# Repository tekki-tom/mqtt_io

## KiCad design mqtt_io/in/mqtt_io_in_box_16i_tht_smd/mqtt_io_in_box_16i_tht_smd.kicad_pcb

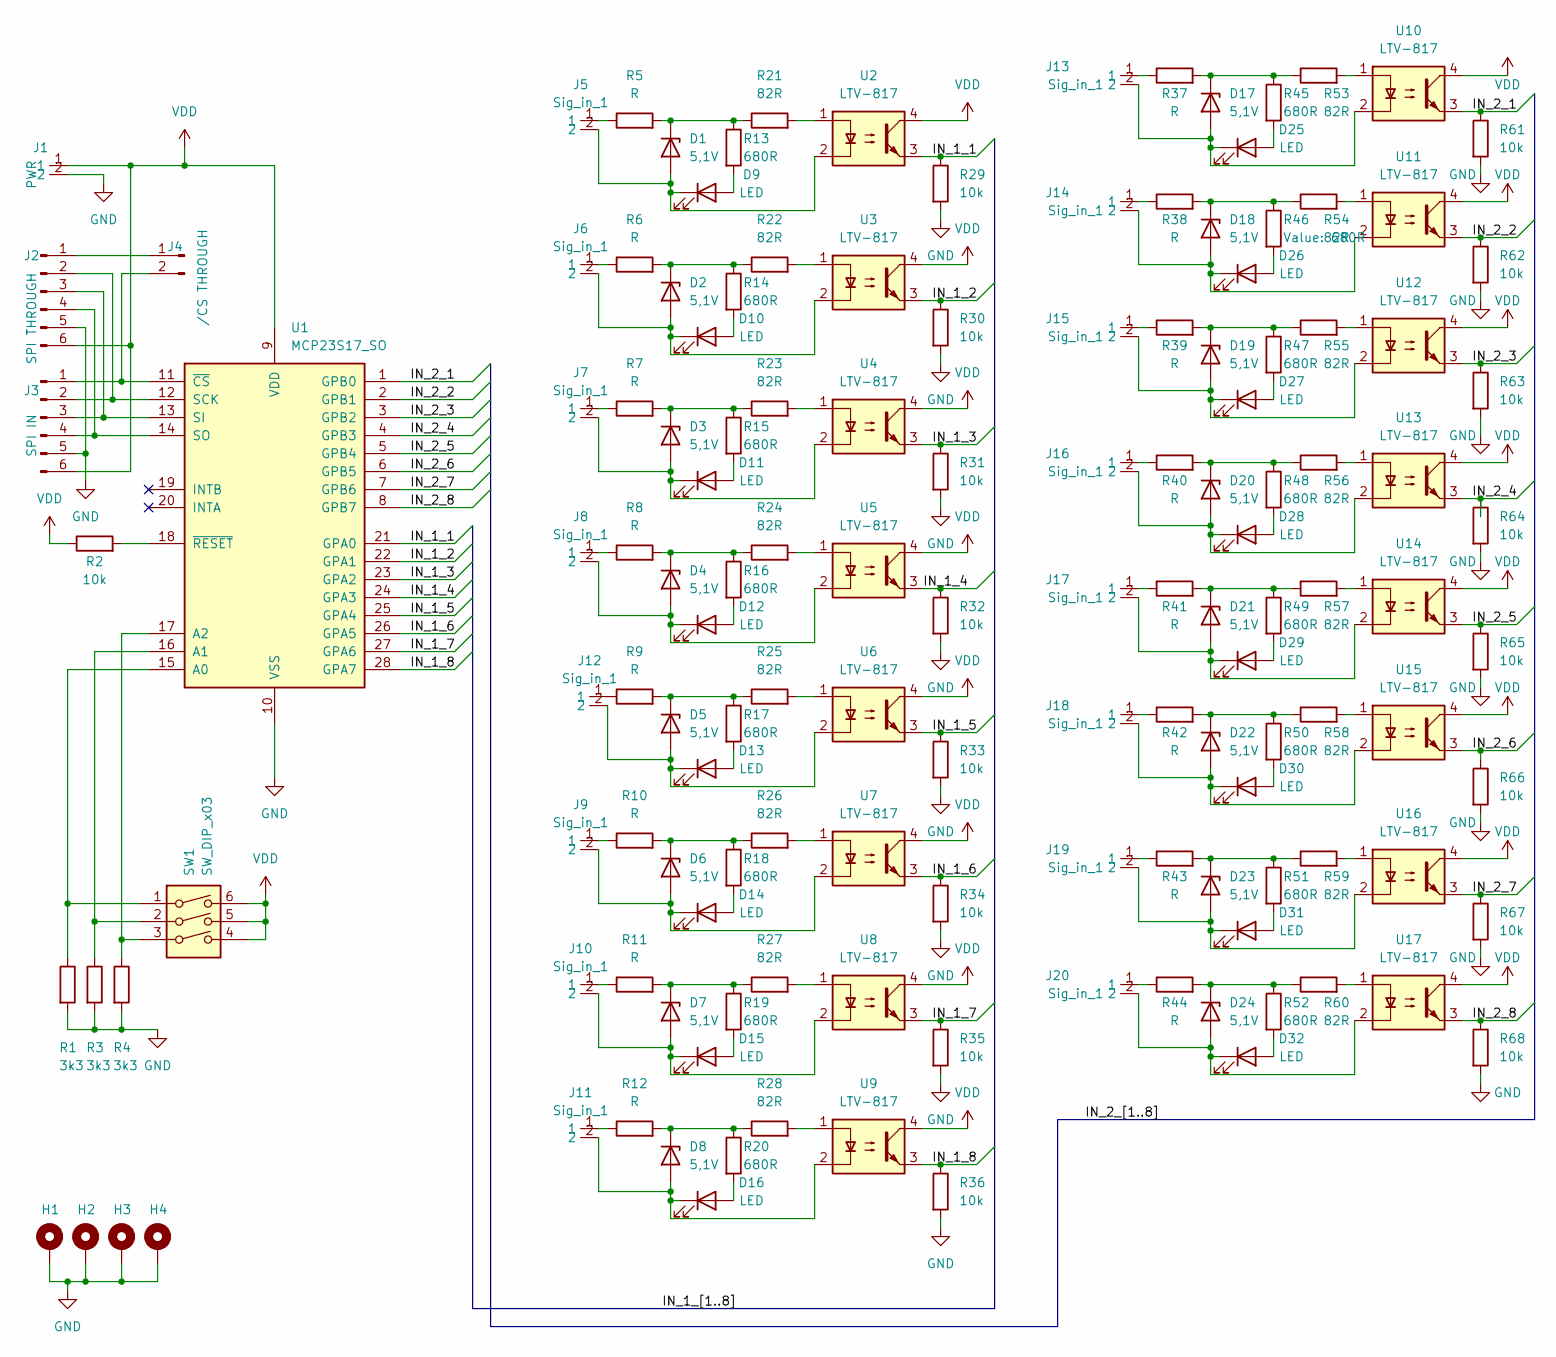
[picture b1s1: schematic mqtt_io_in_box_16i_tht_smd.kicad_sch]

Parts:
D1, D2, D3, D4, D5, D6, D7, D8, D17, D18, D19, D20, D21, D22, D23, D24: 5,1V; D_MiniMELF_Handsoldering
D9, D10, D11, D12, D13, D14, D15, D16, D25, D26, D27, D28, D29, D30, D31, D32: LED; LED_0805_2012Metric_Pad1.15x1.40mm_HandSolder
H1, H2, H3, H4: MountingHole_Pad; MountingHole_3.2mm_M3_DIN965_Pad_TopBottom
J1: PWR; AST_041-2
J2: SPI THROUGH; PinHeader_1x06_P2.54mm_Vertical
J3: SPI IN; PinHeader_1x06_P2.54mm_Vertical
J4: /CS THROUGH; PinHeader_1x02_P2.54mm_Vertical
J5, J6, J7, J8, J9, J10, J11, J12, J13, J14, J15, J16, J17, J18, J19, J20: Sig_in_1; AST_041-2
R1, R3, R4: 3k3; R_0805_2012Metric_Pad1.20x1.40mm_HandSolder
R2, R29, R30, R31, R32, R33, R34, R35, R36, R61, R62, R63, R64, R65, R66, R67, R68: 10k; R_0805_2012Metric_Pad1.20x1.40mm_HandSolder
R5, R6, R7, R8, R9, R10, R11, R12, R37, R38, R39, R40, R41, R42, R43, R44: R; R_0805_2012Metric_Pad1.20x1.40mm_HandSolder
R13, R14, R15, R16, R17, R18, R19, R20, R45, R46, R47, R48, R49, R50, R51, R52: 680R; R_0805_2012Metric_Pad1.20x1.40mm_HandSolder
R21, R22, R23, R24, R25, R26, R27, R28, R53, R54, R55, R56, R57, R58, R59, R60: 82R; R_0805_2012Metric_Pad1.20x1.40mm_HandSolder
SW1: SW_DIP_x03; DIP-6_W7.62mm_LongPads
U1: MCP23S17_SO; SOIC-28W_7.5x17.9mm_P1.27mm
U2, U3, U4, U5, U6, U7, U8, U9, U10, U11, U12, U13, U14, U15, U16, U17: LTV-817; DIP-4_W7.62mm

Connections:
/IN_1_1: R29.1, U1.21 (GPA0), U2.3
/IN_1_2: R30.1, U1.22 (GPA1), U3.3
/IN_1_3: R31.1, U1.23 (GPA2), U4.3
/IN_1_4: R32.1, U1.24 (GPA3), U5.3
/IN_1_5: R33.1, U1.25 (GPA4), U6.3
/IN_1_6: R34.1, U1.26 (GPA5), U7.3
/IN_1_7: R35.1, U1.27 (GPA6), U8.3
/IN_1_8: R36.1, U1.28 (GPA7), U9.3
/IN_2_1: R61.1, U1.1 (GPB0), U10.3
/IN_2_2: R62.1, U1.2 (GPB1), U11.3
/IN_2_3: R63.1, U1.3 (GPB2), U12.3
/IN_2_4: R64.1, U1.4 (GPB3), U13.3
/IN_2_5: R65.1, U1.5 (GPB4), U14.3
/IN_2_6: R66.1, U1.6 (GPB5), U15.3
/IN_2_7: R67.1, U1.7 (GPB6), U16.3
/IN_2_8: R68.1, U1.8 (GPB7), U17.3
GND: H1.1, H2.1, H3.1, H4.1, J1.2, J2.5, J3.5, R1.2, R3.2, R4.2, R29.2, R30.2, R31.2, R32.2, R33.2, R34.2, R35.2, R36.2, R61.2, R62.2, R63.2, R64.2, R65.2, R66.2, R67.2, R68.2, U1.10 (VSS)
unnamed: D1.2 (A), D9.1 (K), J5.2, U2.2
unnamed: D1.1 (K), R5.2, R13.1, R21.1
unnamed: D2.1 (K), R6.2, R14.1, R22.1
unnamed: D3.1 (K), R7.2, R15.1, R23.1
unnamed: D4.1 (K), R8.2, R16.1, R24.1
unnamed: D5.1 (K), R9.2, R17.1, R25.1
unnamed: D6.1 (K), R10.2, R18.1, R26.1
unnamed: D7.1 (K), R11.2, R19.1, R27.1
unnamed: D8.1 (K), R12.2, R20.1, R28.1
unnamed: D9.2 (A), R13.2
unnamed: D10.2 (A), R14.2
unnamed: D2.2 (A), D10.1 (K), J6.2, U3.2
unnamed: D11.2 (A), R15.2
unnamed: D3.2 (A), D11.1 (K), J7.2, U4.2
unnamed: D12.2 (A), R16.2
unnamed: D4.2 (A), D12.1 (K), J8.2, U5.2
unnamed: D13.2 (A), R17.2
unnamed: D5.2 (A), D13.1 (K), J12.2, U6.2
unnamed: D14.2 (A), R18.2
unnamed: D6.2 (A), D14.1 (K), J9.2, U7.2
unnamed: D15.2 (A), R19.2
unnamed: D7.2 (A), D15.1 (K), J10.2, U8.2
unnamed: D16.2 (A), R20.2
unnamed: D8.2 (A), D16.1 (K), J11.2, U9.2
unnamed: D17.2 (A), D25.1 (K), J13.2, U10.2
unnamed: D17.1 (K), R37.2, R45.1, R53.1
unnamed: D18.2 (A), D26.1 (K), J14.2, U11.2
unnamed: D18.1 (K), R38.2, R46.1, R54.1
unnamed: D19.2 (A), D27.1 (K), J15.2, U12.2
unnamed: D19.1 (K), R39.2, R47.1, R55.1
unnamed: D20.2 (A), D28.1 (K), J16.2, U13.2
unnamed: D20.1 (K), R40.2, R48.1, R56.1
unnamed: D21.2 (A), D29.1 (K), J17.2, U14.2
unnamed: D21.1 (K), R41.2, R49.1, R57.1
unnamed: D22.2 (A), D30.1 (K), J18.2, U15.2
unnamed: D22.1 (K), R42.2, R50.1, R58.1
unnamed: D23.2 (A), D31.1 (K), J19.2, U16.2
unnamed: D23.1 (K), R43.2, R51.1, R59.1
unnamed: D24.2 (A), D32.1 (K), J20.2, U17.2
unnamed: D24.1 (K), R44.2, R52.1, R60.1
unnamed: D25.2 (A), R45.2
unnamed: D26.2 (A), R46.2
unnamed: D27.2 (A), R47.2
unnamed: D28.2 (A), R48.2
unnamed: D29.2 (A), R49.2
unnamed: D30.2 (A), R50.2
unnamed: D31.2 (A), R51.2
unnamed: D32.2 (A), R52.2
unnamed: J2.1, J4.1
unnamed: J2.2, J3.2, U1.12 (SCK)
unnamed: J2.3, J3.3, U1.13 (SI)
unnamed: J2.4, J3.4, U1.14 (SO)
unnamed: J3.1, J4.2, U1.11 (~CS)
unnamed: J5.1, R5.1
unnamed: J6.1, R6.1
unnamed: J7.1, R7.1
unnamed: J8.1, R8.1
unnamed: J9.1, R10.1
unnamed: J10.1, R11.1
unnamed: J11.1, R12.1
unnamed: J12.1, R9.1
unnamed: J13.1, R37.1
unnamed: J14.1, R38.1
unnamed: J15.1, R39.1
unnamed: J16.1, R40.1
unnamed: J17.1, R41.1
unnamed: J18.1, R42.1
unnamed: J19.1, R43.1
unnamed: J20.1, R44.1
unnamed: R21.2, U2.1
unnamed: R22.2, U3.1
unnamed: R23.2, U4.1
unnamed: R24.2, U5.1
unnamed: R25.2, U6.1
unnamed: R26.2, U7.1
unnamed: R27.2, U8.1
unnamed: R28.2, U9.1
unnamed: R53.2, U10.1
unnamed: R54.2, U11.1
unnamed: R55.2, U12.1
unnamed: R56.2, U13.1
unnamed: R57.2, U14.1
unnamed: R58.2, U15.1
unnamed: R59.2, U16.1
unnamed: R60.2, U17.1
unnamed: R1.1, SW1.1, U1.15 (A0)
unnamed: R3.1, SW1.2, U1.16 (A1)
unnamed: R4.1, SW1.3, U1.17 (A2)
unnamed: R2.2, U1.18 (~RESET)
VDD: J1.1, J2.6, J3.6, R2.1, SW1.4, SW1.5, SW1.6, U1.9 (VDD), U2.4, U3.4, U4.4, U5.4, U6.4, U7.4, U8.4, U9.4, U10.4, U11.4, U12.4, U13.4, U14.4, U15.4, U16.4, U17.4

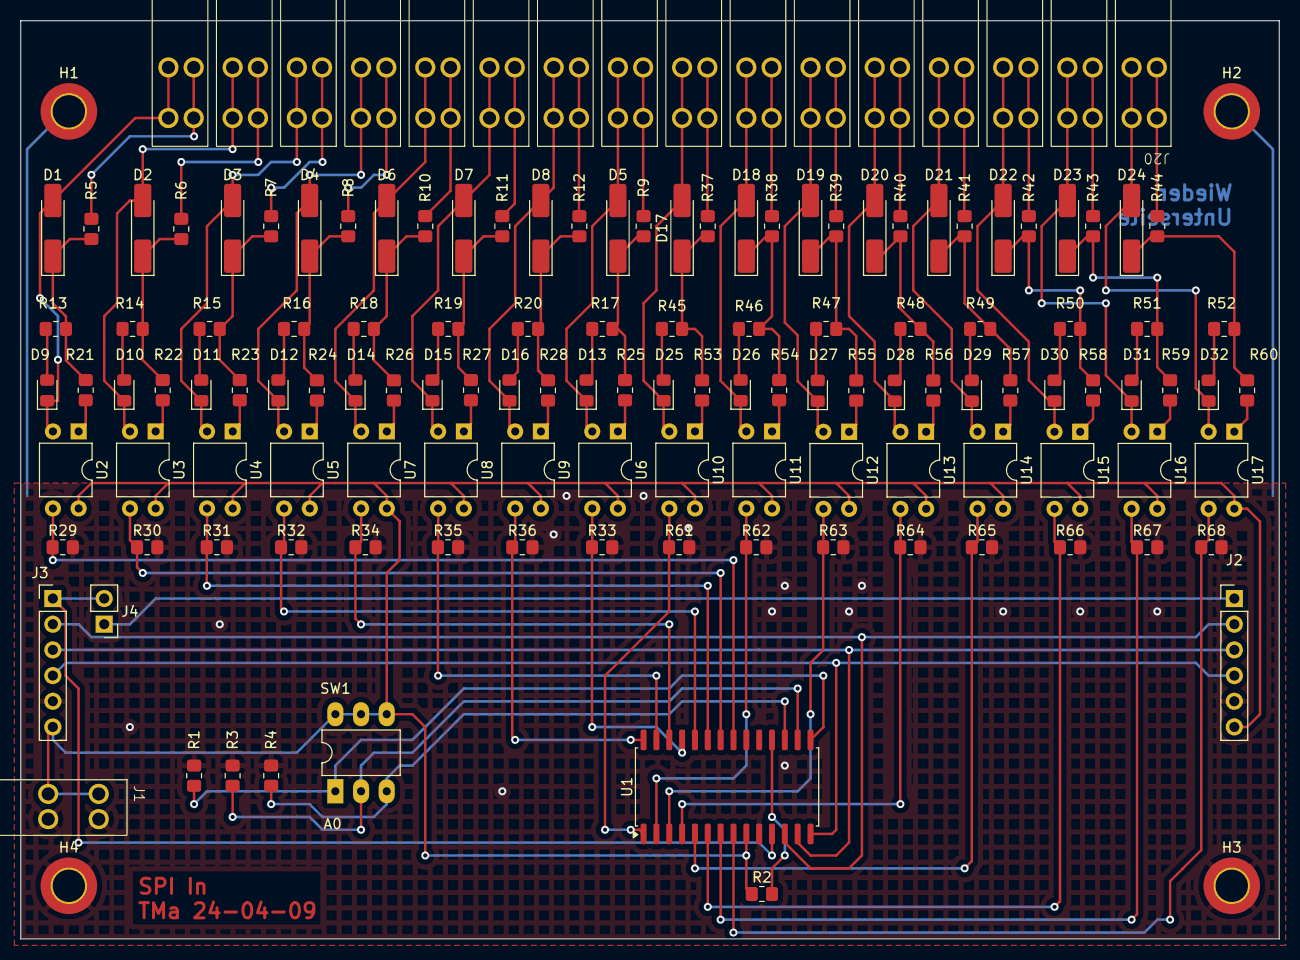
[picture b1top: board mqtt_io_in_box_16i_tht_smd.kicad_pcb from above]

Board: 2 copper layers, 124.5 x 90.8 mm, 142 parts (0 on the bottom side), 107 nets.

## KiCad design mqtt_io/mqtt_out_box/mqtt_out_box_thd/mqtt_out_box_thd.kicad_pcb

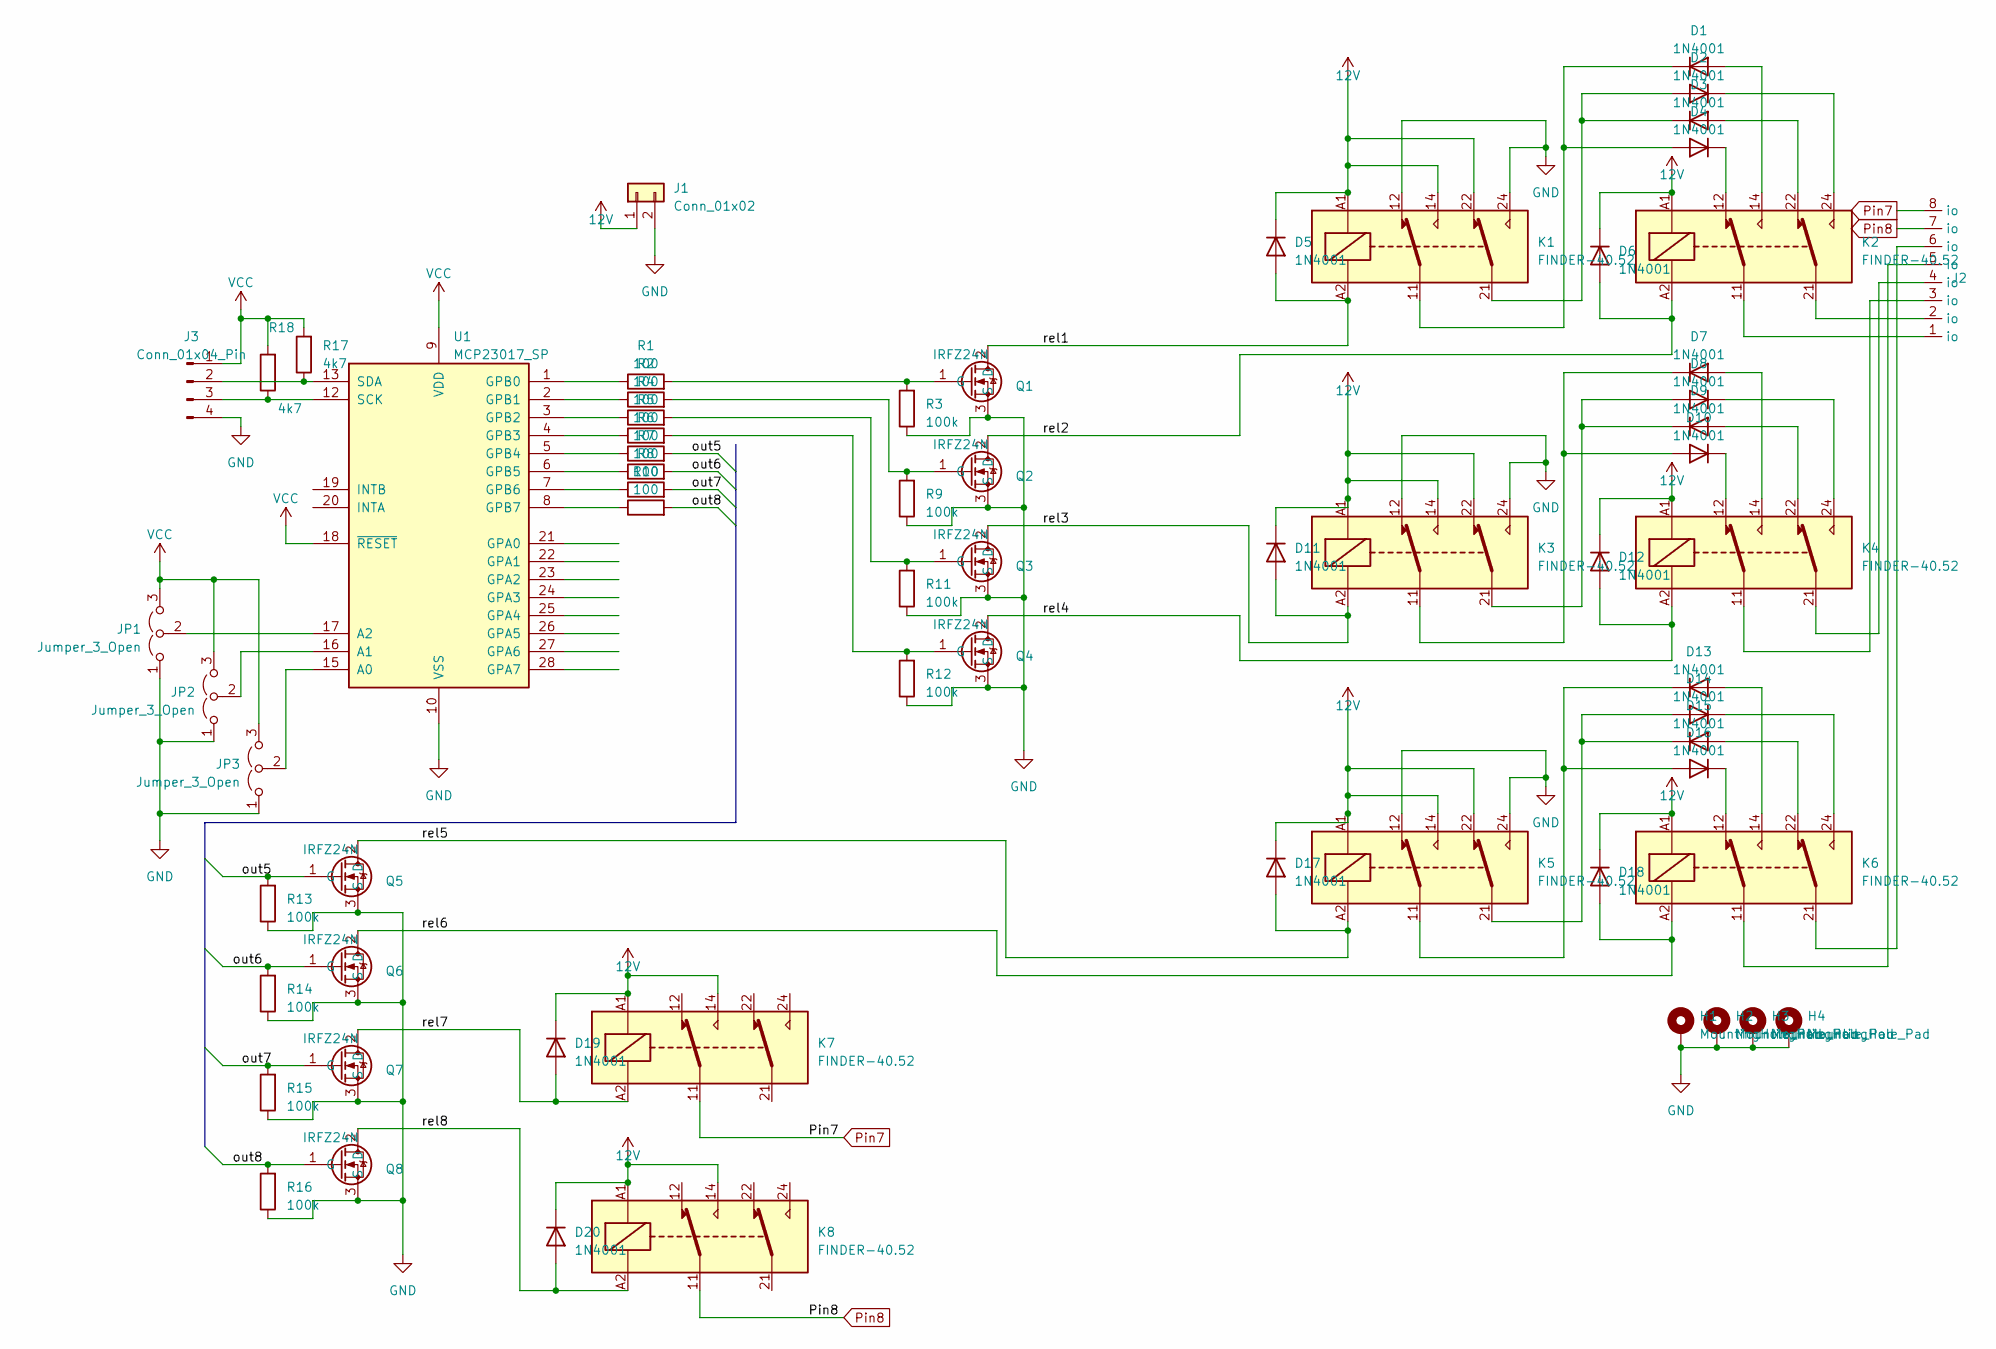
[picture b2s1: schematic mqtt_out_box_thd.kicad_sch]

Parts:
D1, D2, D3, D4, D5, D6, D7, D8, D9, D10, D11, D12, D13, D14, D15, D16, D17, D18, D19, D20: 1N4001; D_DO-41_SOD81_P10.16mm_Horizontal
H1, H2, H3, H4: MountingHole_Pad; MountingHole_3.2mm_M3_ISO7380_Pad_TopBottom
J1: Conn_01x02; PinHeader_1x02_P2.54mm_Vertical
J2: AST041-08
J3: Conn_01x04_Pin; PinHeader_1x04_P2.54mm_Vertical
JP1, JP2, JP3: Jumper_3_Open; PinHeader_1x03_P2.54mm_Vertical
K1, K2, K3, K4, K5, K6, K7, K8: FINDER-40.52; Relay_DPDT_Finder_40.52
Q1, Q2, Q3, Q4, Q5, Q6, Q7, Q8: IRFZ24N; TO-220-3_Vertical
R1, R2, R4, R5, R6, R7, R8, R10: 100; R_Axial_DIN0204_L3.6mm_D1.6mm_P7.62mm_Horizontal
R3, R9, R11, R12, R13, R14, R15, R16: 100k; R_Axial_DIN0204_L3.6mm_D1.6mm_P7.62mm_Horizontal
R17, R18: 4k7; R_Axial_DIN0204_L3.6mm_D1.6mm_P7.62mm_Horizontal
U1: MCP23017_SP; DIP-28_W7.62mm

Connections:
/out5: Q5.1 (G), R6.2, R13.2
/out6: Q6.1 (G), R7.2, R14.2
/out7: Q7.1 (G), R8.2, R15.2
/out8: Q8.1 (G), R10.2, R16.2
/rel1: D5.2 (A), K1.A2, Q1.2 (D)
/rel2: D6.2 (A), K2.A2, Q2.2 (D)
/rel3: D11.2 (A), K3.A2, Q3.2 (D)
/rel4: D12.2 (A), K4.A2, Q4.2 (D)
/rel5: D17.2 (A), K5.A2, Q5.2 (D)
/rel6: D18.2 (A), K6.A2, Q6.2 (D)
/rel7: D19.2 (A), K7.A2, Q7.2 (D)
/rel8: D20.2 (A), K8.A2, Q8.2 (D)
GND: H1.1, H2.1, H3.1, H4.1, J1.2, J3.4, JP1.1 (A), JP2.1 (A), JP3.1 (A), K1.12, K1.24, K3.12, K3.24, K5.12, K5.24, Q1.3 (S), Q2.3 (S), Q3.3 (S), Q4.3 (S), Q5.3 (S), Q6.3 (S), Q7.3 (S), Q8.3 (S), R3.1, R9.1, R11.1, R12.1, R13.1, R14.1, R15.1, R16.1, U1.10 (VSS)
unnamed: D1.2 (A), K2.14
unnamed: D1.1 (K), D4.2 (A), K1.11
unnamed: D2.2 (A), D3.1 (K), K1.21
unnamed: D2.1 (K), K2.24
unnamed: D3.2 (A), K2.22
unnamed: D4.1 (K), K2.12
unnamed: D7.2 (A), K4.14
unnamed: D8.2 (A), D9.1 (K), K3.21
unnamed: D8.1 (K), K4.24
unnamed: D9.2 (A), K4.22
unnamed: D7.1 (K), D10.2 (A), K3.11
unnamed: D10.1 (K), K4.12
unnamed: D13.2 (A), K6.14
unnamed: D13.1 (K), D16.2 (A), K5.11
unnamed: D14.2 (A), D15.1 (K), K5.21
unnamed: D14.1 (K), K6.24
unnamed: D15.2 (A), K6.22
unnamed: D16.1 (K), K6.12
unnamed: J2.1 (io), K2.11
unnamed: J2.2 (io), K2.21
unnamed: J2.3 (io), K4.11
unnamed: J2.4 (io), K4.21
unnamed: J2.5 (io), K6.11
unnamed: J2.6 (io), K6.21
unnamed: J3.2, R17.1, U1.13 (SDA)
unnamed: J3.3, R18.1, U1.12 (SCK)
unnamed: JP1.2 (C), U1.17 (A2)
unnamed: JP2.2 (C), U1.16 (A1)
unnamed: JP3.2 (C), U1.15 (A0)
unnamed: Q1.1 (G), R1.2, R3.2
unnamed: Q2.1 (G), R2.2, R9.2
unnamed: Q3.1 (G), R4.2, R11.2
unnamed: Q4.1 (G), R5.2, R12.2
unnamed: R1.1, U1.1 (GPB0)
unnamed: R2.1, U1.2 (GPB1)
unnamed: R4.1, U1.3 (GPB2)
unnamed: R5.1, U1.4 (GPB3)
unnamed: R6.1, U1.5 (GPB4)
unnamed: R7.1, U1.6 (GPB5)
unnamed: R8.1, U1.7 (GPB6)
unnamed: R10.1, U1.8 (GPB7)
Pin7: J2.8 (io), K7.11
Pin8: J2.7 (io), K8.11
VCC: J3.1, JP1.3 (B), JP2.3 (B), JP3.3 (B), R17.2, R18.2, U1.9 (VDD), U1.18 (~RESET)
VCCQ: D5.1 (K), D6.1 (K), D11.1 (K), D12.1 (K), D17.1 (K), D18.1 (K), D19.1 (K), D20.1 (K), J1.1, K1.14, K1.22, K1.A1, K2.A1, K3.14, K3.22, K3.A1, K4.A1, K5.14, K5.22, K5.A1, K6.A1, K7.14, K7.A1, K8.14, K8.A1

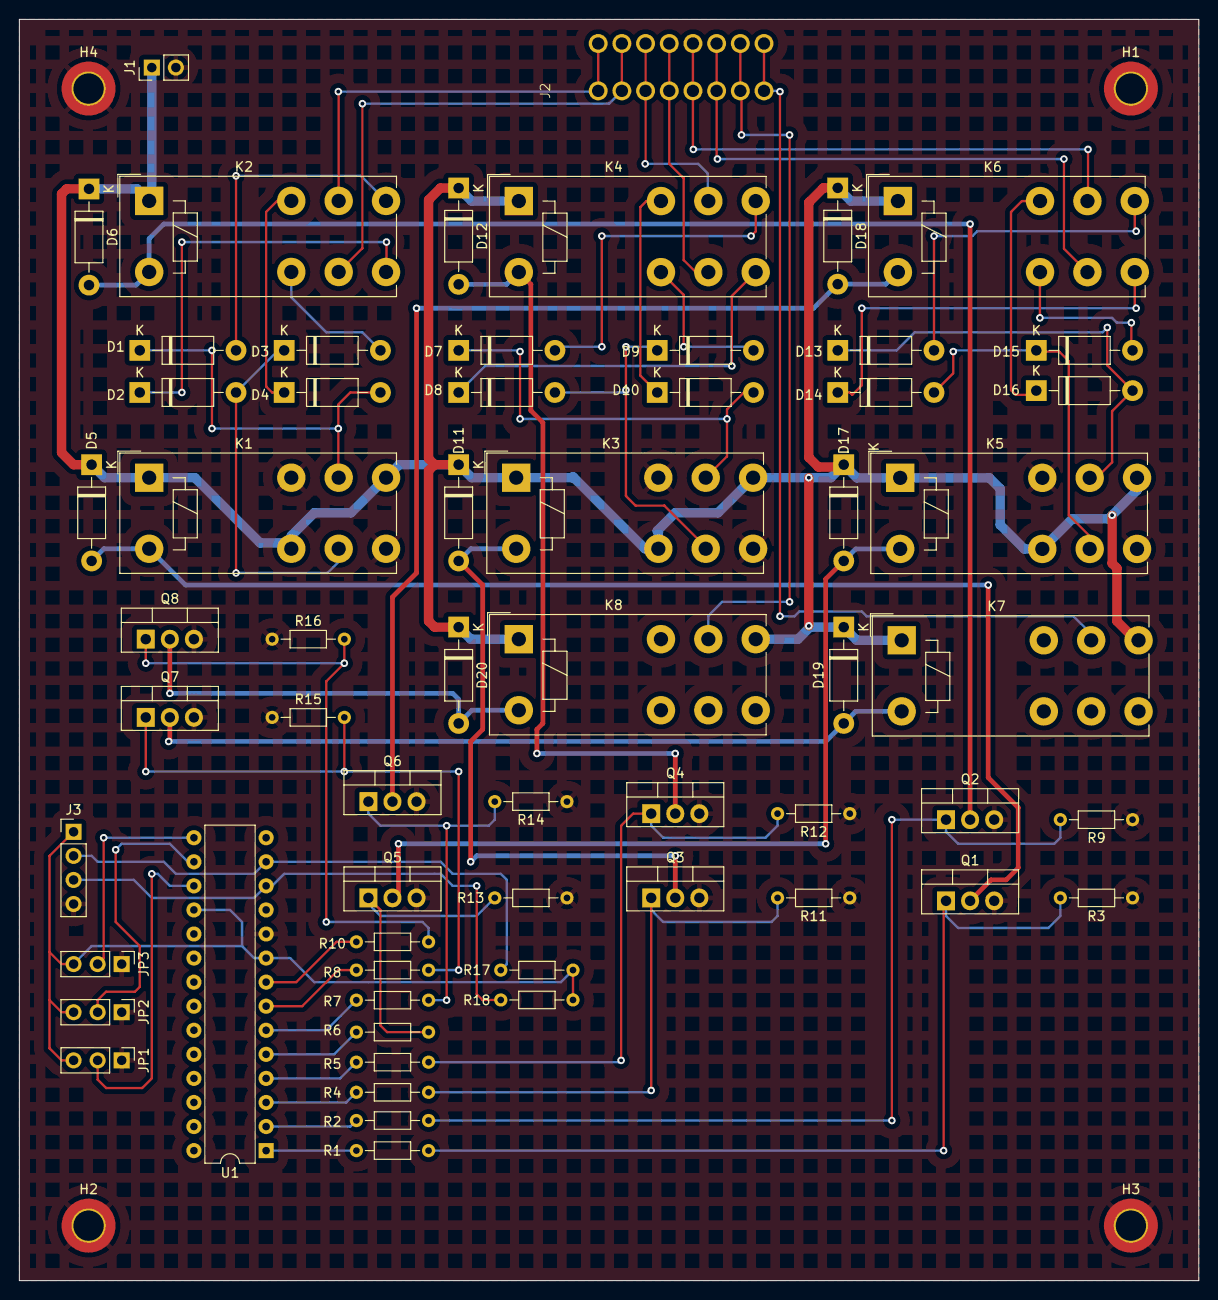
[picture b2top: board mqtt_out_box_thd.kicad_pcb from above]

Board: 2 copper layers, 124.5 x 133.1 mm, 65 parts (0 on the bottom side), 58 nets.

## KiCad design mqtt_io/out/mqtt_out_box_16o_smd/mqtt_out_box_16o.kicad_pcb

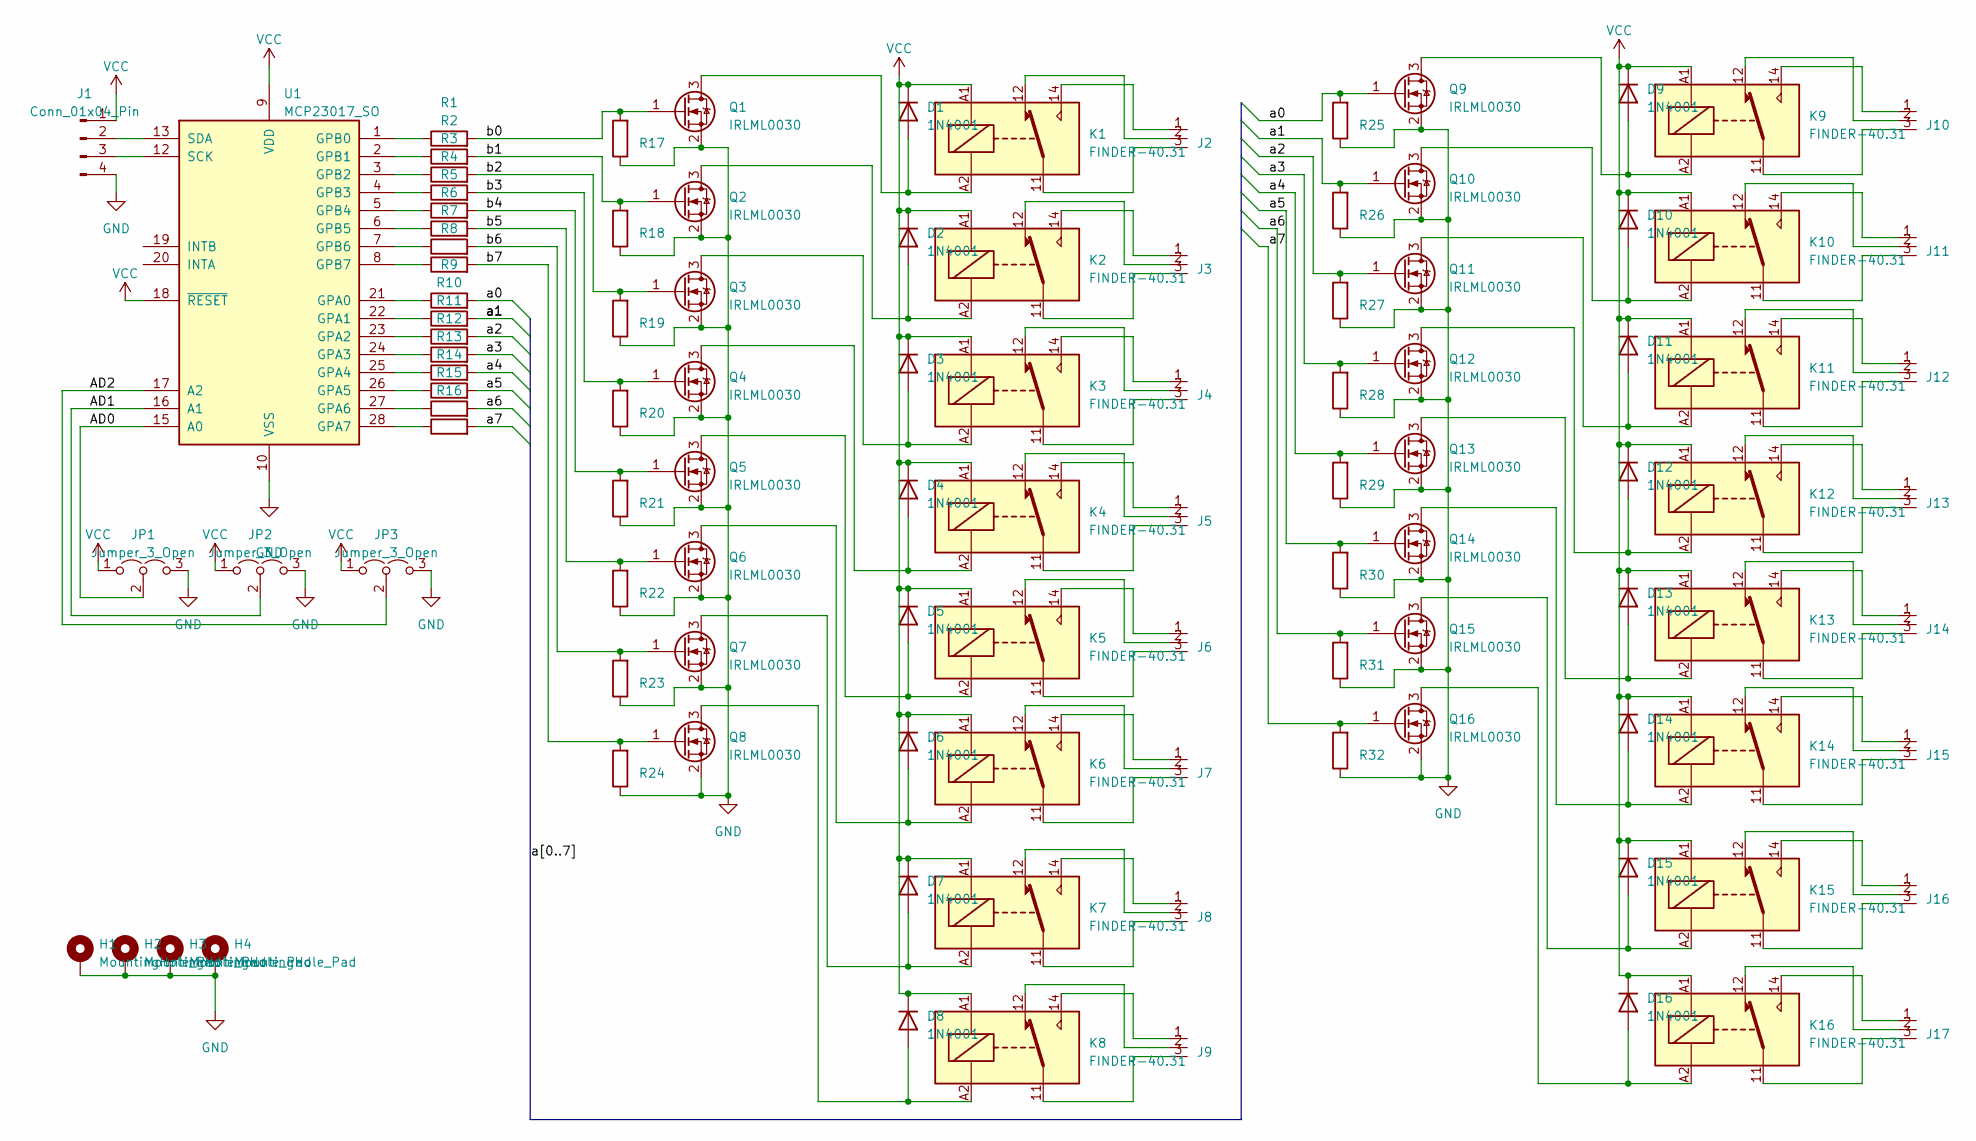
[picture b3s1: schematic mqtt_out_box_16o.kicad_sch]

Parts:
D1, D2, D3, D4, D5, D6, D7, D8, D9, D10, D11, D12, D13, D14, D15, D16: 1N4001; D_DO-41_SOD81_P10.16mm_Horizontal
H1, H2, H3, H4: MountingHole_Pad; MountingHole_3.2mm_M3_DIN965_Pad_TopBottom
J1: Conn_01x04_Pin; PinHeader_1x04_P2.54mm_Vertical
J2, J3, J4, J5, J6, J7, J8, J9, J10, J11, J12, J13, J14, J15, J16, J17: AST_041-3
JP1, JP2, JP3: Jumper_3_Open; PinHeader_1x03_P2.54mm_Vertical
K1, K2, K3, K4, K5, K6, K7, K8, K9, K10, K11, K12, K13, K14, K15, K16: FINDER-40.31; Relay_SPDT_Finder_40.31
Q1, Q2, Q3, Q4, Q5, Q6, Q7, Q8, Q9, Q10, Q11, Q12, Q13, Q14, Q15, Q16: IRLML0030; SOT-23
R1, R2, R3, R4, R5, R6, R7, R8, R9, R10, R11, R12, R13, R14, R15, R16: 100R; R_1206_3216Metric_Pad1.30x1.75mm_HandSolder
R17, R18, R19, R20, R21, R22, R23, R24, R25, R26, R27, R28, R29, R30, R31, R32: 100kR; R_1206_3216Metric_Pad1.30x1.75mm_HandSolder
U1: MCP23017_SO; SOIC-28W_7.5x17.9mm_P1.27mm

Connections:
/AD0: JP1.2 (C), U1.15 (A0)
/AD1: JP2.2 (C), U1.16 (A1)
/AD2: JP3.2 (C), U1.17 (A2)
/a0: Q9.1 (G), R9.2, R25.2
/a1: Q10.1 (G), R10.2, R26.2
/a2: Q11.1 (G), R11.2, R27.2
/a3: Q12.1 (G), R12.2, R28.2
/a4: Q13.1 (G), R13.2, R29.2
/a5: Q14.1 (G), R14.2, R30.2
/a6: Q15.1 (G), R15.2, R31.2
/a7: Q16.1 (G), R16.2, R32.2
/b0: Q1.1 (G), R1.2, R17.2
/b1: Q2.1 (G), R2.2, R18.2
/b2: Q3.1 (G), R3.2, R19.2
/b3: Q4.1 (G), R4.2, R20.2
/b4: Q5.1 (G), R5.2, R21.2
/b5: Q6.1 (G), R6.2, R22.2
/b6: Q7.1 (G), R7.2, R23.2
/b7: Q8.1 (G), R8.2, R24.2
GND: H1.1, H2.1, H3.1, H4.1, J1.4, JP1.3 (B), JP2.3 (B), JP3.3 (B), Q1.2 (S), Q2.2 (S), Q3.2 (S), Q4.2 (S), Q5.2 (S), Q6.2 (S), Q7.2 (S), Q8.2 (S), Q9.2 (S), Q10.2 (S), Q11.2 (S), Q12.2 (S), Q13.2 (S), Q14.2 (S), Q15.2 (S), Q16.2 (S), R17.1, R18.1, R19.1, R20.1, R21.1, R22.1, R23.1, R24.1, R25.1, R26.1, R27.1, R28.1, R29.1, R30.1, R31.1, R32.1, U1.10 (VSS)
unnamed: D1.2 (A), K1.A2, Q1.3 (D)
unnamed: D2.2 (A), K2.A2, Q2.3 (D)
unnamed: D3.2 (A), K3.A2, Q3.3 (D)
unnamed: D4.2 (A), K4.A2, Q4.3 (D)
unnamed: D5.2 (A), K5.A2, Q5.3 (D)
unnamed: D6.2 (A), K6.A2, Q6.3 (D)
unnamed: D7.2 (A), K7.A2, Q7.3 (D)
unnamed: D8.2 (A), K8.A2, Q8.3 (D)
unnamed: D9.2 (A), K9.A2, Q9.3 (D)
unnamed: D10.2 (A), K10.A2, Q10.3 (D)
unnamed: D11.2 (A), K11.A2, Q11.3 (D)
unnamed: D12.2 (A), K12.A2, Q12.3 (D)
unnamed: D13.2 (A), K13.A2, Q13.3 (D)
unnamed: D14.2 (A), K14.A2, Q14.3 (D)
unnamed: D15.2 (A), K15.A2, Q15.3 (D)
unnamed: D16.2 (A), K16.A2, Q16.3 (D)
unnamed: J1.2, U1.13 (SDA)
unnamed: J1.3, U1.12 (SCK)
unnamed: J2.1, K1.14
unnamed: J2.2, K1.12
unnamed: J2.3, K1.11
unnamed: J3.1, K2.14
unnamed: J3.2, K2.12
unnamed: J3.3, K2.11
unnamed: J4.1, K3.14
unnamed: J4.2, K3.12
unnamed: J4.3, K3.11
unnamed: J5.1, K4.14
unnamed: J5.2, K4.12
unnamed: J5.3, K4.11
unnamed: J6.1, K5.14
unnamed: J6.2, K5.12
unnamed: J6.3, K5.11
unnamed: J7.1, K6.14
unnamed: J7.2, K6.12
unnamed: J7.3, K6.11
unnamed: J8.1, K7.14
unnamed: J8.2, K7.12
unnamed: J8.3, K7.11
unnamed: J9.1, K8.14
unnamed: J9.2, K8.12
unnamed: J9.3, K8.11
unnamed: J10.1, K9.14
unnamed: J10.2, K9.12
unnamed: J10.3, K9.11
unnamed: J11.1, K10.14
unnamed: J11.2, K10.12
unnamed: J11.3, K10.11
unnamed: J12.1, K11.14
unnamed: J12.2, K11.12
unnamed: J12.3, K11.11
unnamed: J13.1, K12.14
unnamed: J13.2, K12.12
unnamed: J13.3, K12.11
unnamed: J14.1, K13.14
unnamed: J14.2, K13.12
unnamed: J14.3, K13.11
unnamed: J15.1, K14.14
unnamed: J15.2, K14.12
unnamed: J15.3, K14.11
unnamed: J16.1, K15.14
unnamed: J16.2, K15.12
unnamed: J16.3, K15.11
unnamed: J17.1, K16.14
unnamed: J17.2, K16.12
unnamed: J17.3, K16.11
unnamed: R9.1, U1.21 (GPA0)
unnamed: R10.1, U1.22 (GPA1)
unnamed: R11.1, U1.23 (GPA2)
unnamed: R12.1, U1.24 (GPA3)
unnamed: R13.1, U1.25 (GPA4)
unnamed: R14.1, U1.26 (GPA5)
unnamed: R15.1, U1.27 (GPA6)
unnamed: R16.1, U1.28 (GPA7)
unnamed: R1.1, U1.1 (GPB0)
unnamed: R2.1, U1.2 (GPB1)
unnamed: R3.1, U1.3 (GPB2)
unnamed: R4.1, U1.4 (GPB3)
unnamed: R5.1, U1.5 (GPB4)
unnamed: R6.1, U1.6 (GPB5)
unnamed: R7.1, U1.7 (GPB6)
unnamed: R8.1, U1.8 (GPB7)
VCC: D1.1 (K), D2.1 (K), D3.1 (K), D4.1 (K), D5.1 (K), D6.1 (K), D7.1 (K), D8.1 (K), D9.1 (K), D10.1 (K), D11.1 (K), D12.1 (K), D13.1 (K), D14.1 (K), D15.1 (K), D16.1 (K), J1.1, JP1.1 (A), JP2.1 (A), JP3.1 (A), K1.A1, K2.A1, K3.A1, K4.A1, K5.A1, K6.A1, K7.A1, K8.A1, K9.A1, K10.A1, K11.A1, K12.A1, K13.A1, K14.A1, K15.A1, K16.A1, U1.9 (VDD), U1.18 (~RESET)

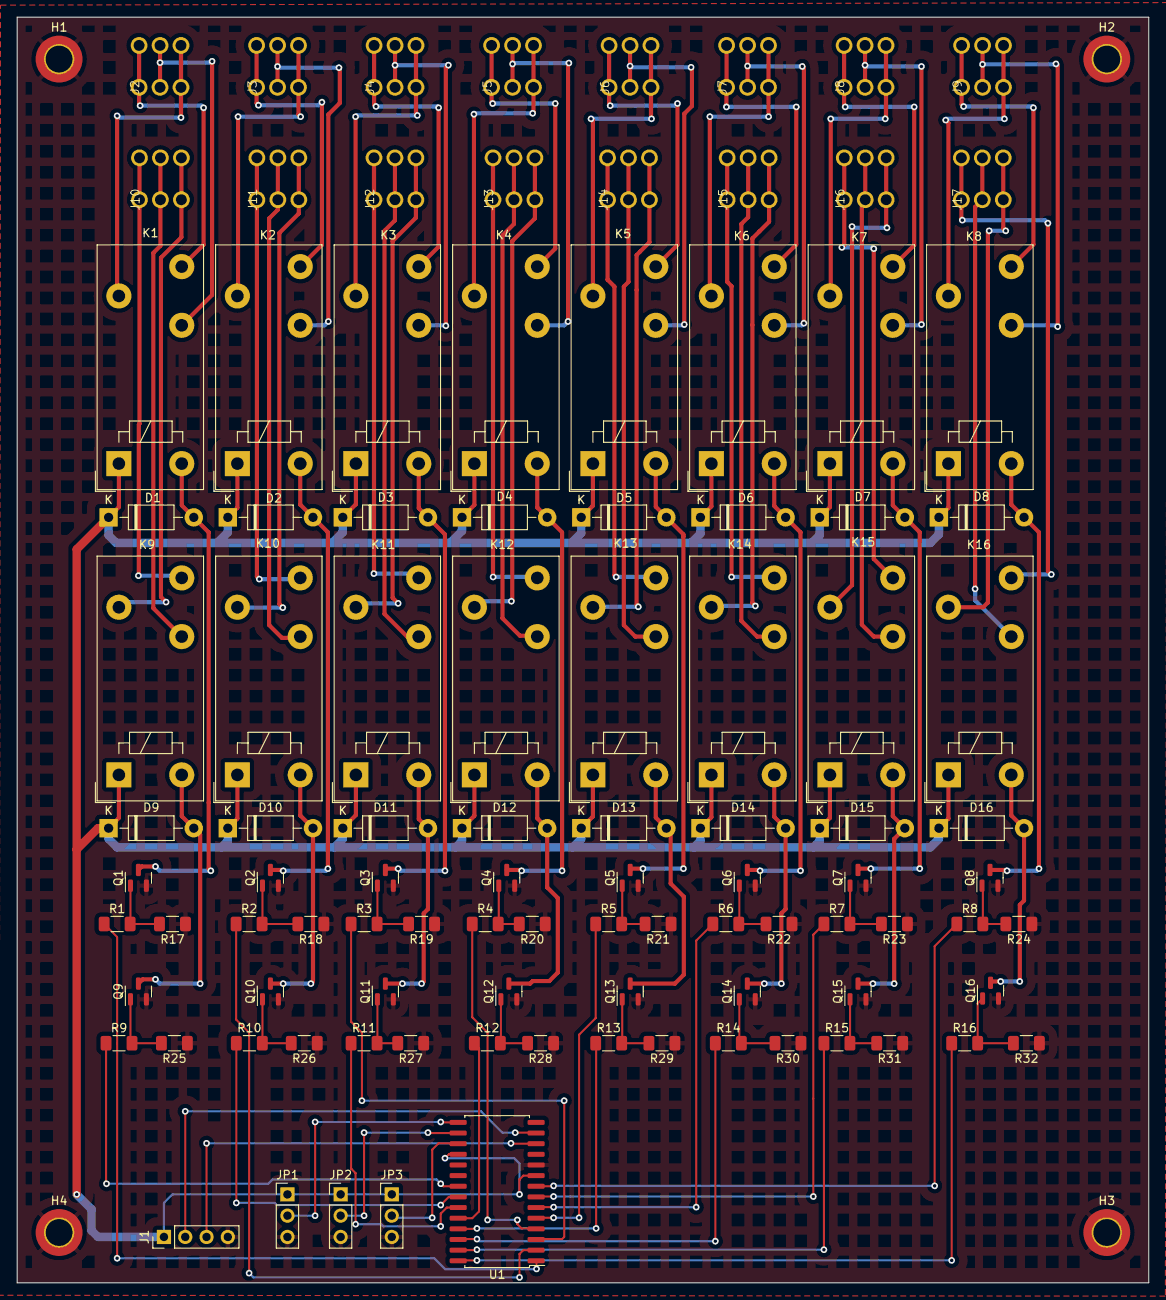
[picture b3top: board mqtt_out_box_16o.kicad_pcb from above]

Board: 2 copper layers, 135.0 x 151.0 mm, 105 parts (0 on the bottom side), 103 nets.
